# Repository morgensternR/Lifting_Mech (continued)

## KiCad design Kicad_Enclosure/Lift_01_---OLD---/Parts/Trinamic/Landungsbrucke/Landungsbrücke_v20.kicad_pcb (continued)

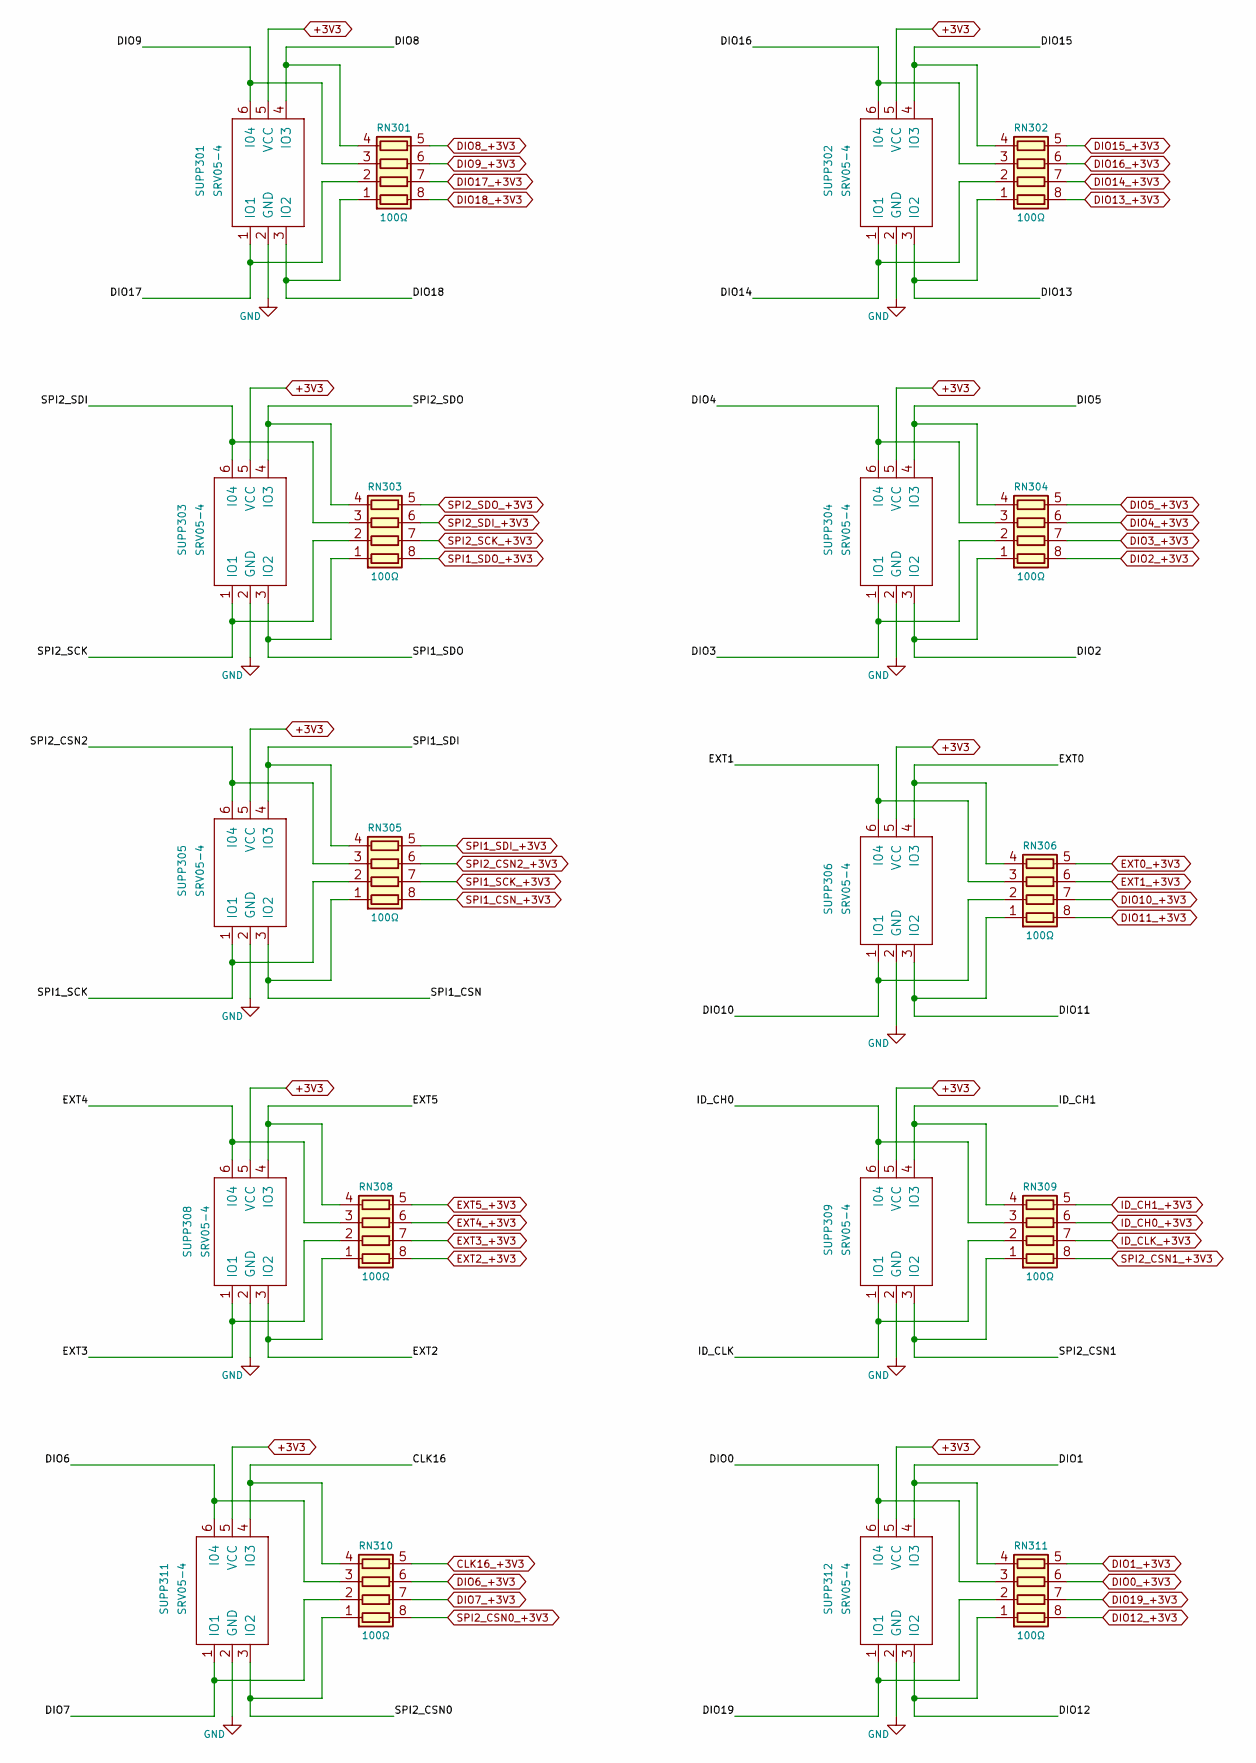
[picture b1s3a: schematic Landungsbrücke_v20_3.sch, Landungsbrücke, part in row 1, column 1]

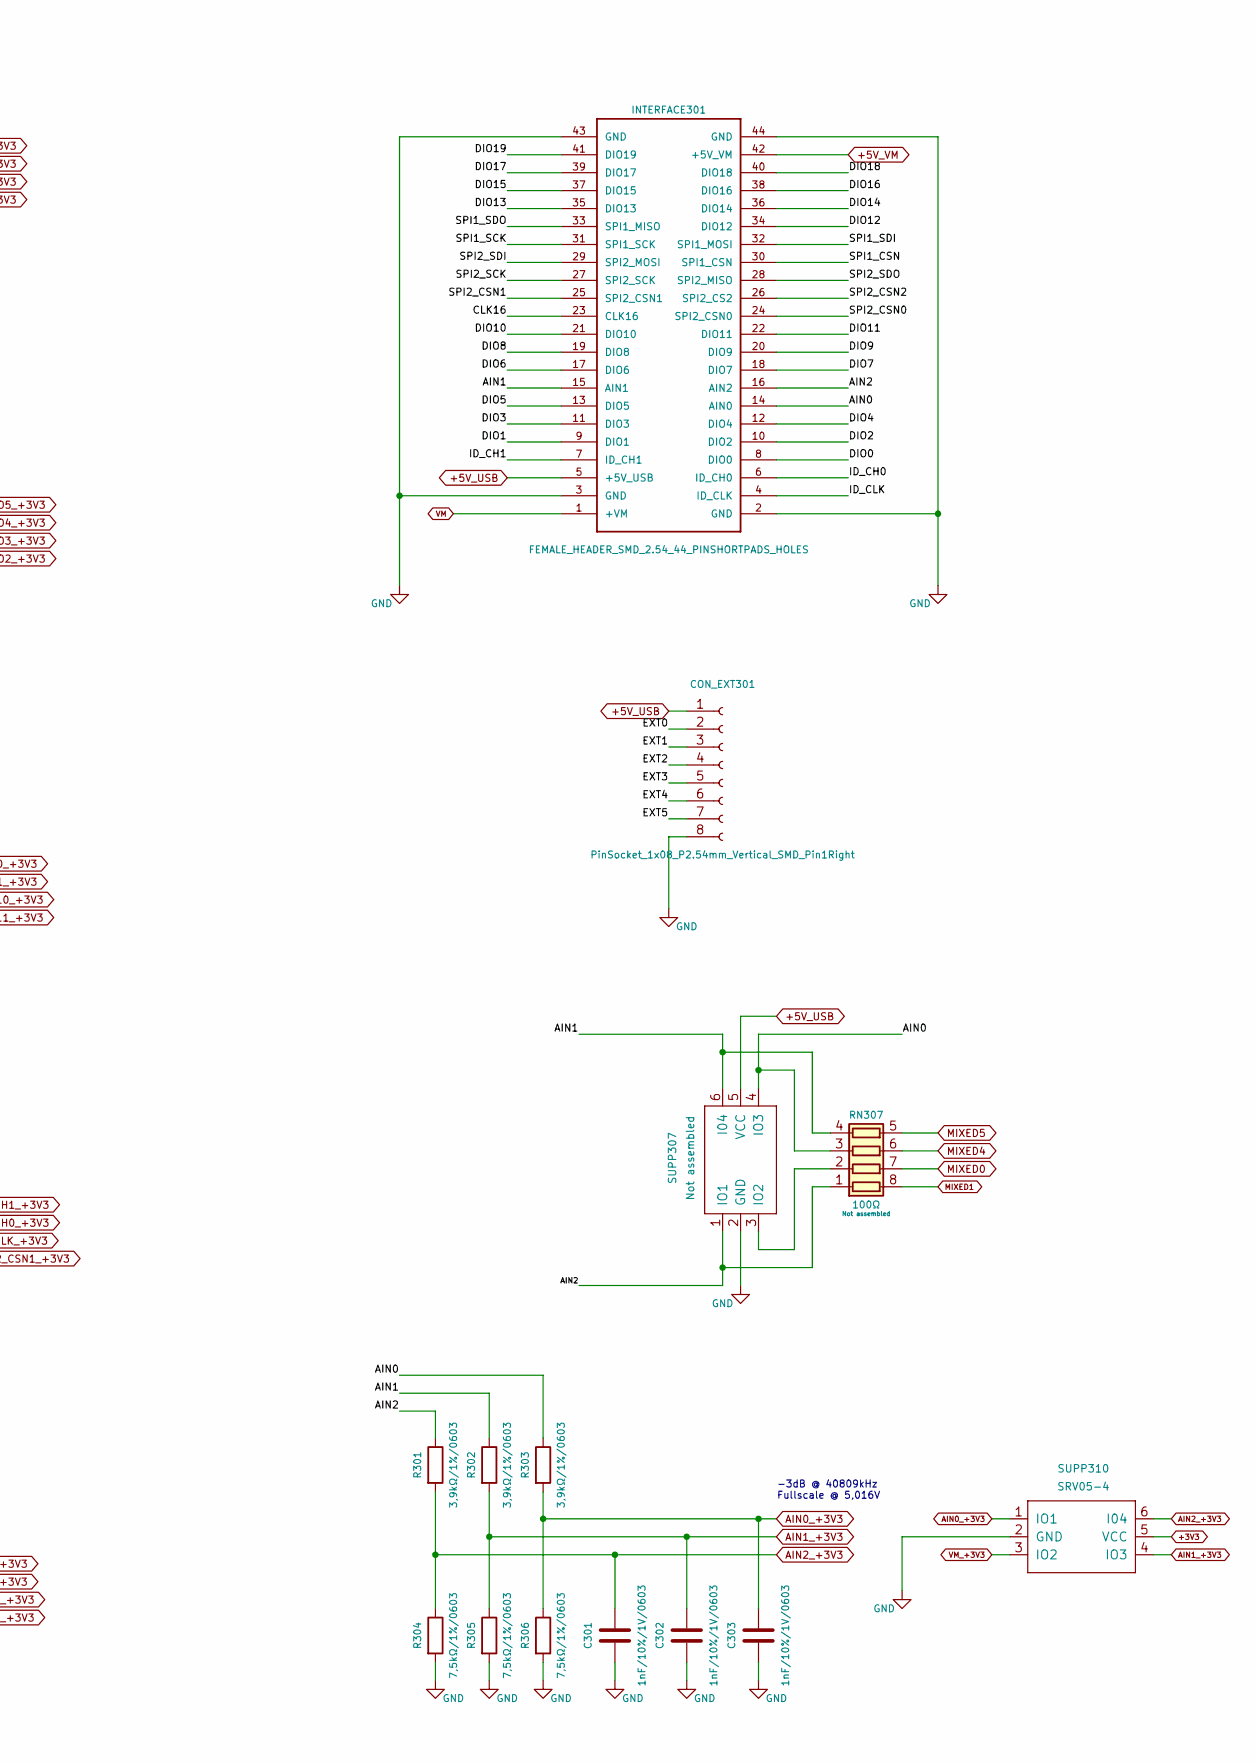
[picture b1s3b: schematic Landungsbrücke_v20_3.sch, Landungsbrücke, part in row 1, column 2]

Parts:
C301, C302, C303: 1nF/10%/1V/0603; C_0603_1608Metric
CON_EXT301: PinSocket_1x08_P2.54mm_Vertical_SMD_Pin1Right
INTERFACE301: FEMALE_HEADER_SMD_2.54_44_PINSHORTPADS_HOLES; Samtec_HLE-122-02-xxx-DV-BE-A_2x22_P2.54mm_Horizontal
R301, R302, R303: 3,9kΩ/1%/0603; R_0603_1608Metric
R304, R305, R306: 7,5kΩ/1%/0603; R_0603_1608Metric
RN301, RN302, RN303, RN304, RN305, RN306, RN307, RN308, RN309, RN310, RN311: 100Ω; R_Array_Concave_4x0603
SUPP301, SUPP302, SUPP303, SUPP304, SUPP305, SUPP306, SUPP308, SUPP309, SUPP310, SUPP311, SUPP312: SRV05-4; SOT-23-6
SUPP307: Not assembled; SOT-23-6

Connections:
+3V3: SUPP301.5 (VCC), SUPP302.5 (VCC), SUPP303.5 (VCC), SUPP304.5 (VCC), SUPP305.5 (VCC), SUPP306.5 (VCC), SUPP308.5 (VCC), SUPP309.5 (VCC), SUPP310.5 (VCC), SUPP311.5 (VCC), SUPP312.5 (VCC); also elsewhere on the board
+5V_USB: CON_EXT301.1, INTERFACE301.5 (+5V_USB), SUPP307.5 (VCC); also elsewhere on the board
+5V_VM: INTERFACE301.42 (+5V_VM); also elsewhere on the board
/Landungsbrücke_v20_3/AIN0: INTERFACE301.14 (AIN0), R303.1, RN307.3 (R3.1), SUPP307.4 (IO3)
/Landungsbrücke_v20_3/AIN1: INTERFACE301.15 (AIN1), R302.1, RN307.4 (R4.1), SUPP307.6 (I04)
/Landungsbrücke_v20_3/AIN2: INTERFACE301.16 (AIN2), R301.1, RN307.1 (R1.1), SUPP307.1 (IO1)
/Landungsbrücke_v20_3/CLK16: INTERFACE301.23 (CLK16), RN310.4 (R4.1), SUPP311.4 (IO3)
/Landungsbrücke_v20_3/DIO0: INTERFACE301.8 (DIO0), RN311.3 (R3.1), SUPP312.6 (I04)
/Landungsbrücke_v20_3/DIO1: INTERFACE301.9 (DIO1), RN311.4 (R4.1), SUPP312.4 (IO3)
/Landungsbrücke_v20_3/DIO2: INTERFACE301.10 (DIO2), RN304.1 (R1.1), SUPP304.3 (IO2)
/Landungsbrücke_v20_3/DIO3: INTERFACE301.11 (DIO3), RN304.2 (R2.1), SUPP304.1 (IO1)
/Landungsbrücke_v20_3/DIO4: INTERFACE301.12 (DIO4), RN304.3 (R3.1), SUPP304.6 (I04)
/Landungsbrücke_v20_3/DIO5: INTERFACE301.13 (DIO5), RN304.4 (R4.1), SUPP304.4 (IO3)
/Landungsbrücke_v20_3/DIO6: INTERFACE301.17 (DIO6), RN310.3 (R3.1), SUPP311.6 (I04)
/Landungsbrücke_v20_3/DIO7: INTERFACE301.18 (DIO7), RN310.2 (R2.1), SUPP311.1 (IO1)
/Landungsbrücke_v20_3/DIO8: INTERFACE301.19 (DIO8), RN301.4 (R4.1), SUPP301.4 (IO3)
/Landungsbrücke_v20_3/DIO9: INTERFACE301.20 (DIO9), RN301.3 (R3.1), SUPP301.6 (I04)
/Landungsbrücke_v20_3/DIO10: INTERFACE301.21 (DIO10), RN306.2 (R2.1), SUPP306.1 (IO1)
/Landungsbrücke_v20_3/DIO11: INTERFACE301.22 (DIO11), RN306.1 (R1.1), SUPP306.3 (IO2)
/Landungsbrücke_v20_3/DIO12: INTERFACE301.34 (DIO12), RN311.1 (R1.1), SUPP312.3 (IO2)
/Landungsbrücke_v20_3/DIO13: INTERFACE301.35 (DIO13), RN302.1 (R1.1), SUPP302.3 (IO2)
/Landungsbrücke_v20_3/DIO14: INTERFACE301.36 (DIO14), RN302.2 (R2.1), SUPP302.1 (IO1)
/Landungsbrücke_v20_3/DIO15: INTERFACE301.37 (DIO15), RN302.4 (R4.1), SUPP302.4 (IO3)
/Landungsbrücke_v20_3/DIO16: INTERFACE301.38 (DIO16), RN302.3 (R3.1), SUPP302.6 (I04)
/Landungsbrücke_v20_3/DIO17: INTERFACE301.39 (DIO17), RN301.2 (R2.1), SUPP301.1 (IO1)
/Landungsbrücke_v20_3/DIO18: INTERFACE301.40 (DIO18), RN301.1 (R1.1), SUPP301.3 (IO2)
/Landungsbrücke_v20_3/DIO19: INTERFACE301.41 (DIO19), RN311.2 (R2.1), SUPP312.1 (IO1)
/Landungsbrücke_v20_3/EXT0: CON_EXT301.2, RN306.4 (R4.1), SUPP306.4 (IO3)
/Landungsbrücke_v20_3/EXT1: CON_EXT301.3, RN306.3 (R3.1), SUPP306.6 (I04)
/Landungsbrücke_v20_3/EXT2: CON_EXT301.4, RN308.1 (R1.1), SUPP308.3 (IO2)
/Landungsbrücke_v20_3/EXT3: CON_EXT301.5, RN308.2 (R2.1), SUPP308.1 (IO1)
/Landungsbrücke_v20_3/EXT4: CON_EXT301.6, RN308.3 (R3.1), SUPP308.6 (I04)
/Landungsbrücke_v20_3/EXT5: CON_EXT301.7, RN308.4 (R4.1), SUPP308.4 (IO3)
/Landungsbrücke_v20_3/ID_CH0: INTERFACE301.6 (ID_CH0), RN309.3 (R3.1), SUPP309.6 (I04)
/Landungsbrücke_v20_3/ID_CH1: INTERFACE301.7 (ID_CH1), RN309.4 (R4.1), SUPP309.4 (IO3)
/Landungsbrücke_v20_3/ID_CLK: INTERFACE301.4 (ID_CLK), RN309.2 (R2.1), SUPP309.1 (IO1)
/Landungsbrücke_v20_3/SPI1_CSN: INTERFACE301.30 (SPI1_CSN), RN305.1 (R1.1), SUPP305.3 (IO2)
/Landungsbrücke_v20_3/SPI1_SCK: INTERFACE301.31 (SPI1_SCK), RN305.2 (R2.1), SUPP305.1 (IO1)
/Landungsbrücke_v20_3/SPI1_SDI: INTERFACE301.32 (SPI1_MOSI), RN305.4 (R4.1), SUPP305.4 (IO3)
/Landungsbrücke_v20_3/SPI1_SDO: INTERFACE301.33 (SPI1_MISO), RN303.1 (R1.1), SUPP303.3 (IO2)
/Landungsbrücke_v20_3/SPI2_CSN0: INTERFACE301.24 (SPI2_CSN0), RN310.1 (R1.1), SUPP311.3 (IO2)
/Landungsbrücke_v20_3/SPI2_CSN1: INTERFACE301.25 (SPI2_CSN1), RN309.1 (R1.1), SUPP309.3 (IO2)
/Landungsbrücke_v20_3/SPI2_CSN2: INTERFACE301.26 (SPI2_CS2), RN305.3 (R3.1), SUPP305.6 (I04)
/Landungsbrücke_v20_3/SPI2_SCK: INTERFACE301.27 (SPI2_SCK), RN303.2 (R2.1), SUPP303.1 (IO1)
/Landungsbrücke_v20_3/SPI2_SDI: INTERFACE301.29 (SPI2_MOSI), RN303.3 (R3.1), SUPP303.6 (I04)
/Landungsbrücke_v20_3/SPI2_SDO: INTERFACE301.28 (SPI2_MISO), RN303.4 (R4.1), SUPP303.4 (IO3)
AIN0_+3V3: C303.1, R303.2, R306.1, SUPP310.1 (IO1); also elsewhere on the board
AIN1_+3V3: C302.1, R302.2, R305.1, SUPP310.4 (IO3); also elsewhere on the board
AIN2_+3V3: C301.1, R301.2, R304.1, SUPP310.6 (I04); also elsewhere on the board
CLK16_+3V3: RN310.5 (R4.2); also elsewhere on the board
DIO0_+3V3: RN311.6 (R3.2); also elsewhere on the board
DIO1_+3V3: RN311.5 (R4.2); also elsewhere on the board
DIO2_+3V3: RN304.8 (R1.2); also elsewhere on the board
DIO3_+3V3: RN304.7 (R2.2); also elsewhere on the board
DIO4_+3V3: RN304.6 (R3.2); also elsewhere on the board
DIO5_+3V3: RN304.5 (R4.2); also elsewhere on the board
DIO6_+3V3: RN310.6 (R3.2); also elsewhere on the board
DIO7_+3V3: RN310.7 (R2.2); also elsewhere on the board
DIO8_+3V3: RN301.5 (R4.2); also elsewhere on the board
DIO9_+3V3: RN301.6 (R3.2); also elsewhere on the board
DIO10_+3V3: RN306.7 (R2.2); also elsewhere on the board
DIO11_+3V3: RN306.8 (R1.2); also elsewhere on the board
DIO12_+3V3: RN311.8 (R1.2); also elsewhere on the board
DIO13_+3V3: RN302.8 (R1.2); also elsewhere on the board
DIO14_+3V3: RN302.7 (R2.2); also elsewhere on the board
DIO15_+3V3: RN302.5 (R4.2); also elsewhere on the board
DIO16_+3V3: RN302.6 (R3.2); also elsewhere on the board
DIO17_+3V3: RN301.7 (R2.2); also elsewhere on the board
DIO18_+3V3: RN301.8 (R1.2); also elsewhere on the board
DIO19_+3V3: RN311.7 (R2.2); also elsewhere on the board
EXT0_+3V3: RN306.5 (R4.2); also elsewhere on the board
EXT1_+3V3: RN306.6 (R3.2); also elsewhere on the board
EXT2_+3V3: RN308.8 (R1.2); also elsewhere on the board
EXT3_+3V3: RN308.7 (R2.2); also elsewhere on the board
EXT4_+3V3: RN308.6 (R3.2); also elsewhere on the board
EXT5_+3V3: RN308.5 (R4.2); also elsewhere on the board
GND: C301.2, C302.2, C303.2, CON_EXT301.8, INTERFACE301.2 (GND), INTERFACE301.3 (GND), INTERFACE301.43 (GND), INTERFACE301.44 (GND), R304.2, R305.2, R306.2, SUPP301.2 (GND), SUPP302.2 (GND), SUPP303.2 (GND), SUPP304.2 (GND), SUPP305.2 (GND), SUPP306.2 (GND), SUPP307.2 (GND), SUPP308.2 (GND), SUPP309.2 (GND), SUPP310.2 (GND), SUPP311.2 (GND), SUPP312.2 (GND); also elsewhere on the board
ID_CH0_+3V3: RN309.6 (R3.2); also elsewhere on the board
ID_CH1_+3V3: RN309.5 (R4.2); also elsewhere on the board
ID_CLK_+3V3: RN309.7 (R2.2); also elsewhere on the board
MIXED0: RN307.7 (R2.2); also elsewhere on the board
MIXED1: RN307.8 (R1.2); also elsewhere on the board
MIXED4: RN307.6 (R3.2); also elsewhere on the board
MIXED5: RN307.5 (R4.2); also elsewhere on the board
unnamed: RN307.2 (R2.1), SUPP307.3 (IO2)
SPI1_CSN_+3V3: RN305.8 (R1.2); also elsewhere on the board
SPI1_SCK_+3V3: RN305.7 (R2.2); also elsewhere on the board
SPI1_SDI_+3V3: RN305.5 (R4.2); also elsewhere on the board
SPI1_SDO_+3V3: RN303.8 (R1.2); also elsewhere on the board
SPI2_CSN0_+3V3: RN310.8 (R1.2); also elsewhere on the board
SPI2_CSN1_+3V3: RN309.8 (R1.2); also elsewhere on the board
SPI2_CSN2_+3V3: RN305.6 (R3.2); also elsewhere on the board
SPI2_SCK_+3V3: RN303.7 (R2.2); also elsewhere on the board
SPI2_SDI_+3V3: RN303.6 (R3.2); also elsewhere on the board
SPI2_SDO_+3V3: RN303.5 (R4.2); also elsewhere on the board
VM: INTERFACE301.1 (+VM); also elsewhere on the board
VM_+3V3: SUPP310.3 (IO2); also elsewhere on the board

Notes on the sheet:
-3dB @ 40809kHz Fullscale @ 5,016V

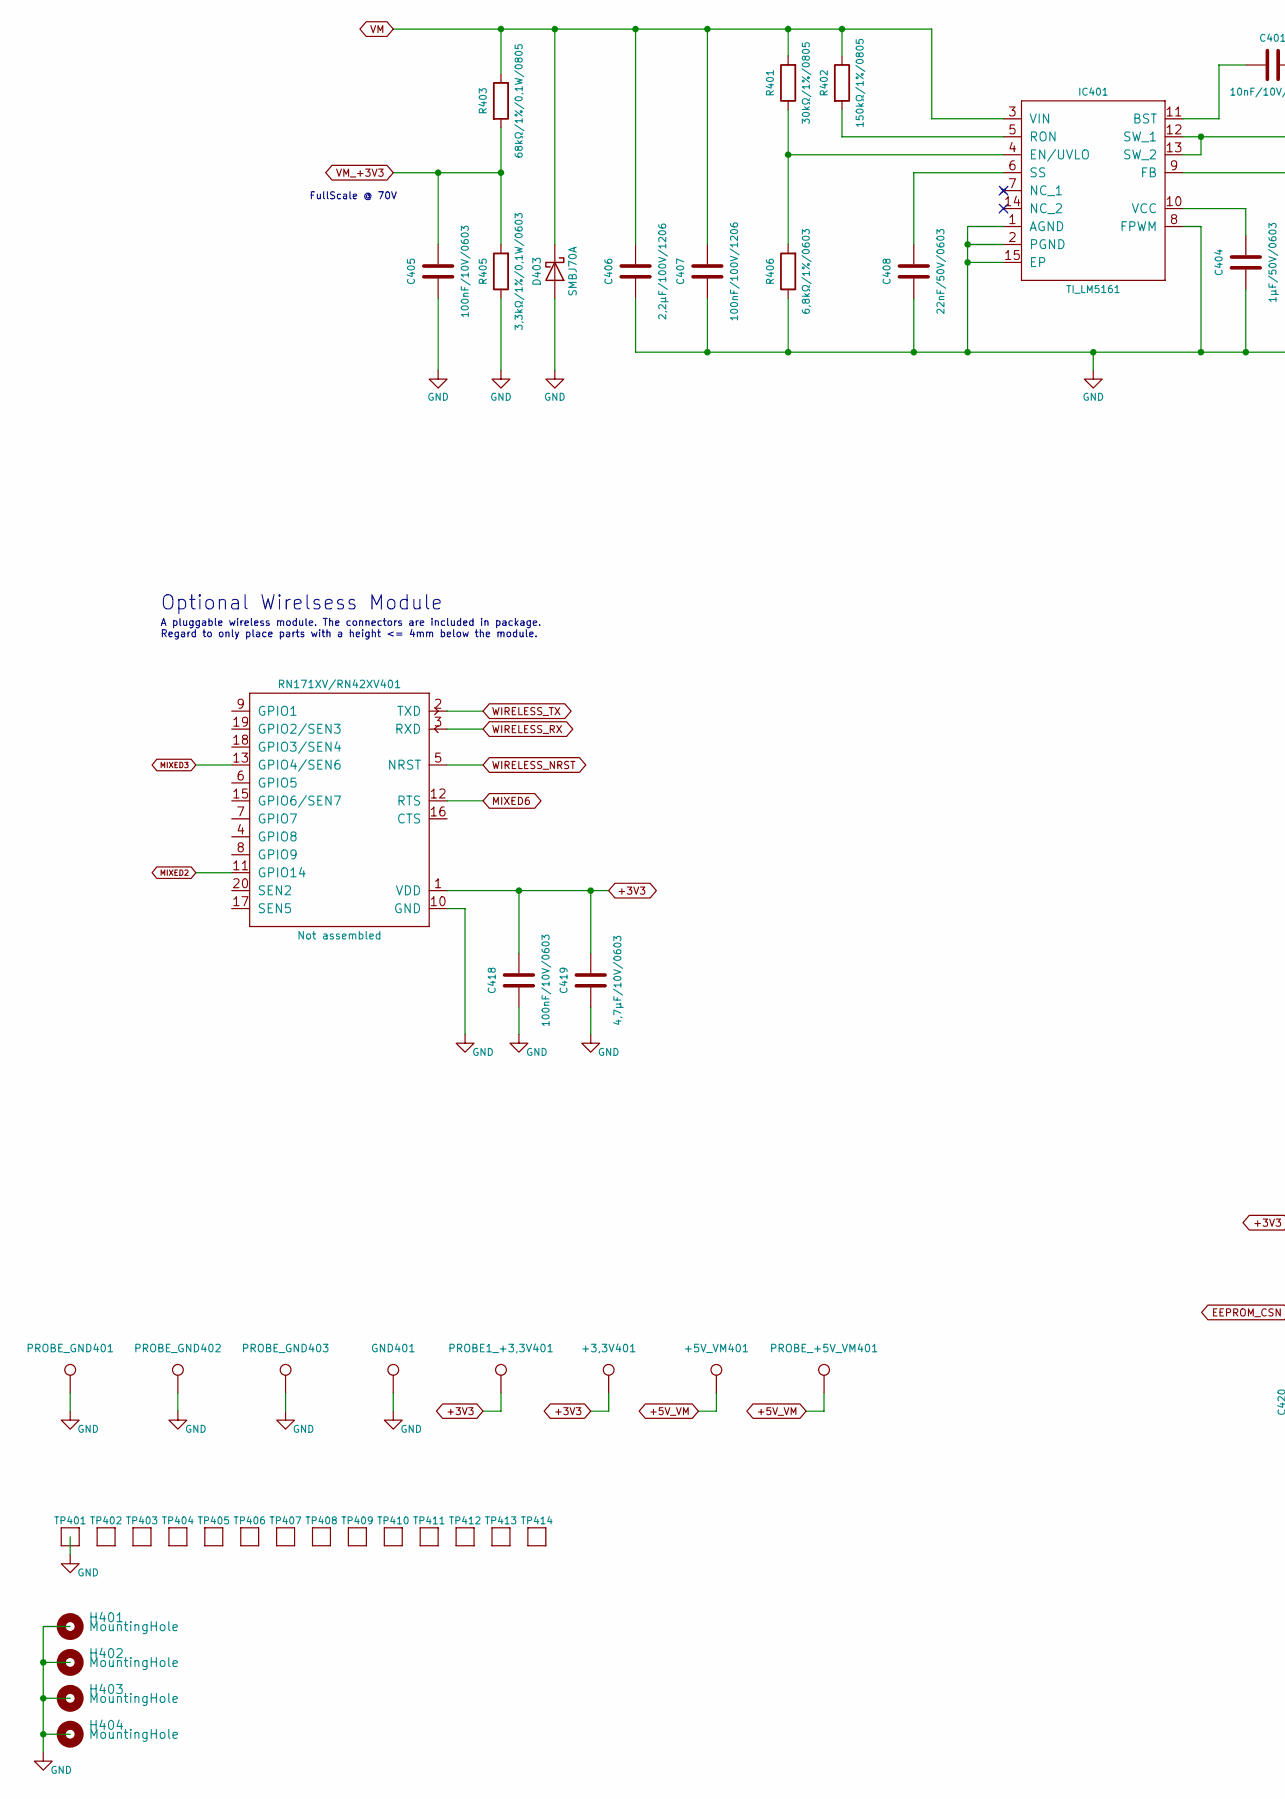
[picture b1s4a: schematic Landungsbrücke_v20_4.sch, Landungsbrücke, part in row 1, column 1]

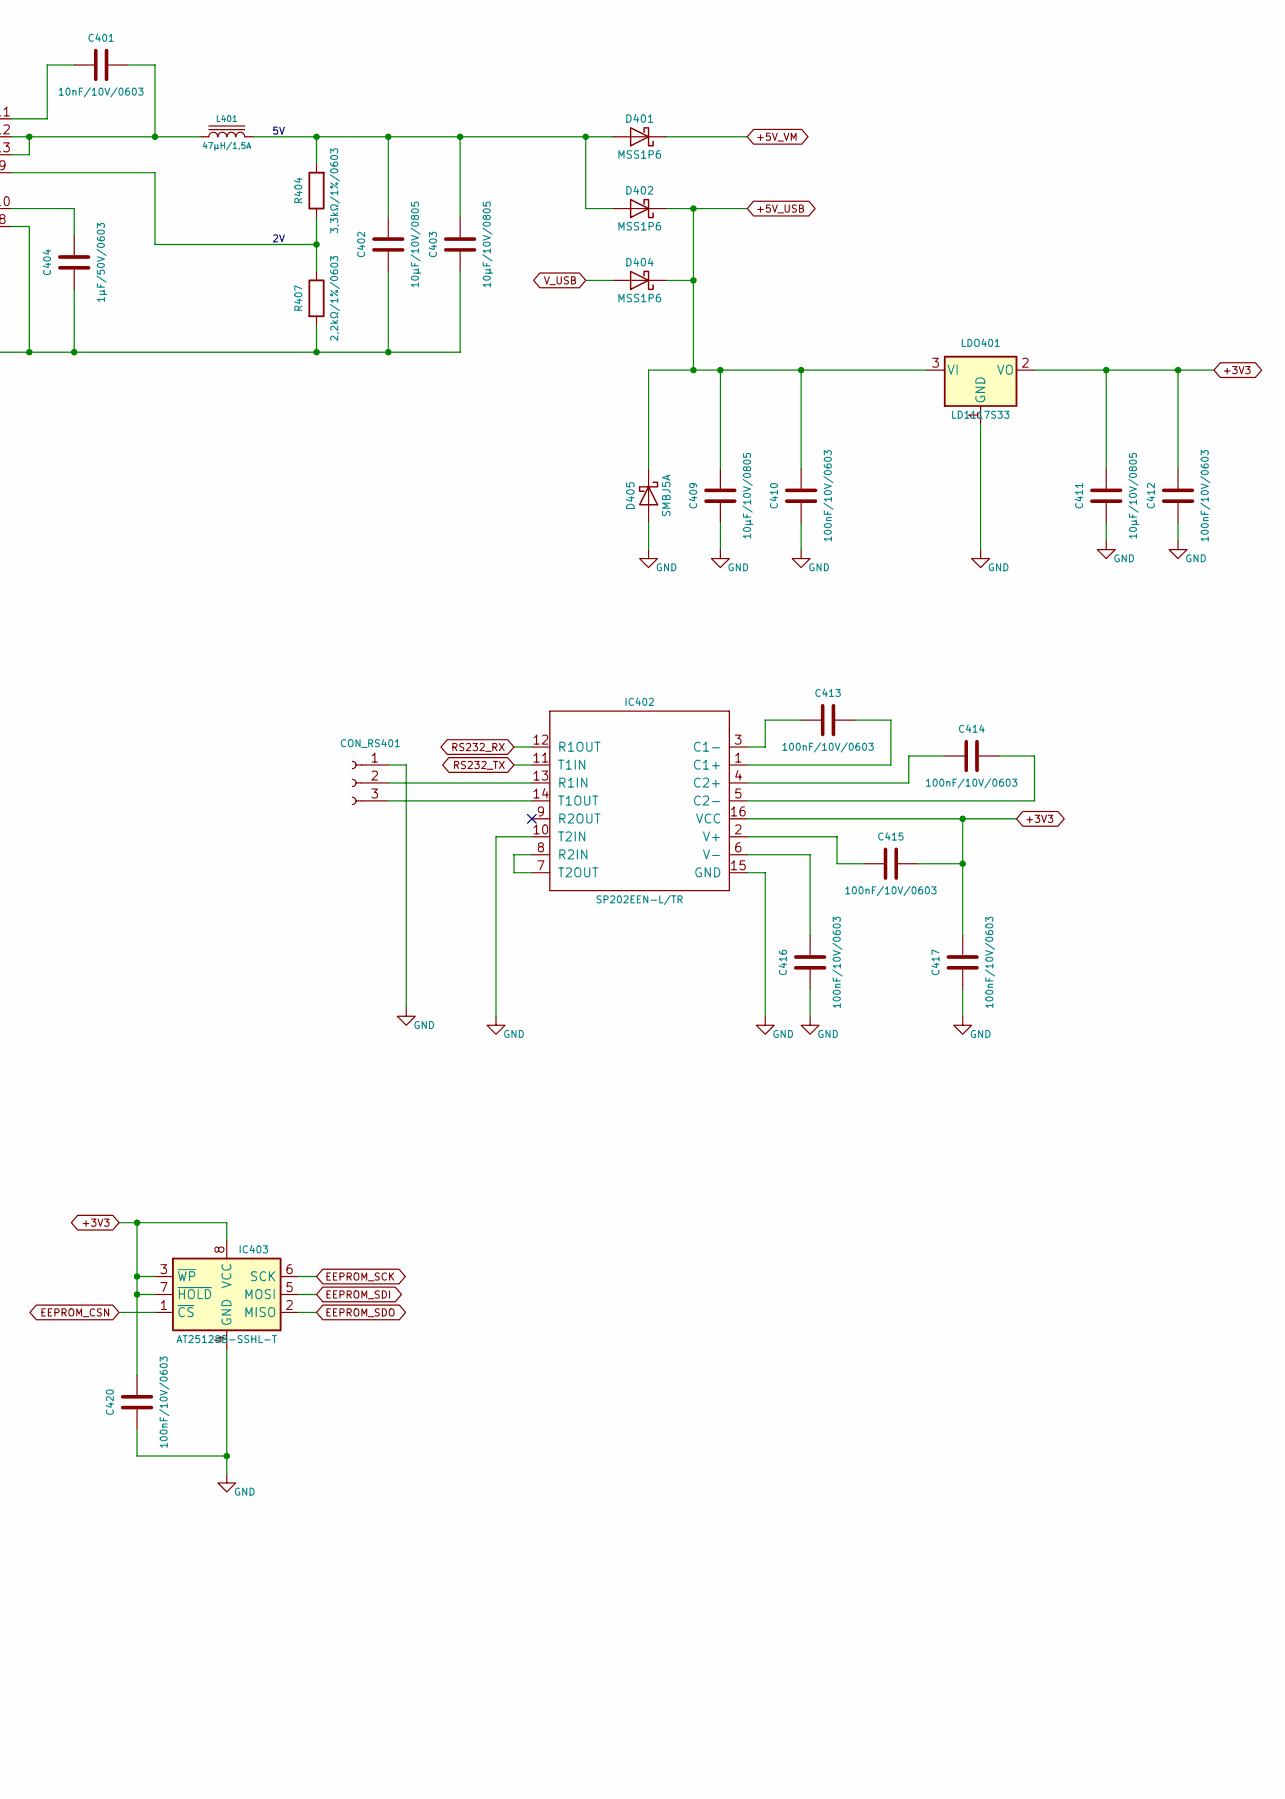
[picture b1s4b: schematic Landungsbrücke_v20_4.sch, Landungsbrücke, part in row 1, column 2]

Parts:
+3,3V401: 1PIN_1ROW; TestPoint_Loop_D1.80mm_Drill1.0mm_Beaded
+5V_VM401: Not assembled; TestPoint_Loop_D1.80mm_Drill1.0mm_Beaded
C401: 10nF/10V/0603; C_0603_1608Metric
C402, C403, C409, C411: 10μF/10V/0805; C_0805_2012Metric
C404: 1μF/50V/0603; C_0603_1608Metric
C405, C410, C412, C413, C414, C415, C416, C417, C418, C420: 100nF/10V/0603; C_0603_1608Metric
C406: 2,2μF/100V/1206; C_1206_3216Metric
C407: 100nF/100V/1206; C_1206_3216Metric
C408: 22nF/50V/0603; C_0603_1608Metric
C419: 4,7µF/10V/0603; C_0603_1608Metric
CON_RS401: PinSocket_1x03_P2.54mm_Vertical_SMD_Pin1Right
D401, D402, D404: MSS1P6; D_TUMD2
D403: SMBJ70A; D_SMB
D405: SMBJ5A; D_SMB
GND401: 1PIN_1ROW; TestPoint_Loop_D1.80mm_Drill1.0mm_Beaded
H401, H402, H403, H404: MountingHole; MountingHole_3.2mm_M3_Pad
IC401: TI_LM5161; TSSOP-14-1EP_4.4x5mm_P0.65mm
IC402: SP202EEN-L/TR; SOIC-16_3.9x9.9mm_P1.27mm
IC403: AT25128B-SSHL-T; SO-8_3.9x4.9mm_P1.27mm
L401: 47μH/1,5A; L_Bourns-SRU8043
LDO401: LD1117S33; SOT-223-3_TabPin2
PROBE1_+3,3V401: Not assembled; TestPoint_Loop_D1.80mm_Drill1.0mm_Beaded
PROBE_+5V_VM401: 1PIN_1ROW; TestPoint_Loop_D1.80mm_Drill1.0mm_Beaded
PROBE_GND401, PROBE_GND402, PROBE_GND403: Not assembled; TestPoint_Loop_D1.80mm_Drill1.0mm_Beaded
R401: 30kΩ/1%/0805; R_0805_2012Metric
R402: 150kΩ/1%/0805; R_0805_2012Metric
R403: 68kΩ/1%/0,1W/0805; R_0805_2012Metric
R404: 3,3kΩ/1%/0603; R_0603_1608Metric
R405: 3,3kΩ/1%/0,1W/0603; R_0603_1608Metric
R406: 6,8kΩ/1%/0603; R_0603_1608Metric
R407: 2,2kΩ/1%/0603; R_0603_1608Metric
RN171XV/RN42XV401: Not assembled; Radio_module
TP401, TP402, TP403, TP404, TP405, TP406, TP407, TP408, TP409, TP410, TP411, TP412, TP413, TP414: Not assembled; PAD_R1.2

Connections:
+3V3: +3,3V401.1, C411.1, C412.1, C415.1, C417.1, C418.1, C419.1, C420.2, IC402.16 (VCC), IC403.3 (~WP), IC403.7 (~HOLD), IC403.8 (VCC), LDO401.2 (VO), PROBE1_+3,3V401.1, RN171XV/RN42XV401.1 (VDD); also elsewhere on the board
+5V_USB: C409.1, C410.1, D402.1 (K), D404.1 (K), D405.1 (K), LDO401.3 (VI); also elsewhere on the board
+5V_VM: +5V_VM401.1, D401.1 (K), PROBE_+5V_VM401.1; also elsewhere on the board
EEPROM_CSN: IC403.1 (~CS); also elsewhere on the board
EEPROM_SCK: IC403.6 (SCK); also elsewhere on the board
EEPROM_SDI: IC403.5 (MOSI); also elsewhere on the board
EEPROM_SDO: IC403.2 (MISO); also elsewhere on the board
GND: C402.2, C403.2, C404.2, C405.2, C406.2, C407.2, C408.2, C409.2, C410.2, C411.2, C412.2, C416.2, C417.2, C418.2, C419.2, C420.1, CON_RS401.1, D403.2 (A), D405.2 (A), GND401.1, H401.~, H402.~, H403.~, H404.~, IC401.1 (AGND), IC401.2 (PGND), IC401.8 (FPWM), IC401.15 (EP), IC402.10 (T2IN), IC402.15 (GND), IC403.4 (GND), LDO401.1 (GND), PROBE_GND401.1, PROBE_GND402.1, PROBE_GND403.1, R405.1, R406.1, R407.2, RN171XV/RN42XV401.10 (GND), TP401.P$1; also elsewhere on the board
MIXED2: RN171XV/RN42XV401.11 (GPIO14); also elsewhere on the board
MIXED3: RN171XV/RN42XV401.13 (GPIO4/SEN6); also elsewhere on the board
MIXED6: RN171XV/RN42XV401.12 (RTS); also elsewhere on the board
unnamed: C401.1, IC401.12 (SW_1), IC401.13 (SW_2), L401.1
unnamed: C401.2, IC401.11 (BST)
unnamed: C402.1, C403.1, D401.2 (A), D402.2 (A), L401.2, R404.2
unnamed: C404.1, IC401.10 (VCC)
unnamed: C408.1, IC401.6 (SS)
unnamed: C413.1, IC402.1 (C1+)
unnamed: C413.2, IC402.3 (C1-)
unnamed: C414.1, IC402.5 (C2-)
unnamed: C414.2, IC402.4 (C2+)
unnamed: C415.2, IC402.2 (V+)
unnamed: C416.1, IC402.6 (V-)
unnamed: CON_RS401.2, IC402.13 (R1IN)
unnamed: CON_RS401.3, IC402.14 (T1OUT)
unnamed: IC401.4 (EN/UVLO), R401.1, R406.2
unnamed: IC401.5 (RON), R402.2
unnamed: IC401.9 (FB), R404.1, R407.1
unnamed: IC402.7 (T2OUT), IC402.8 (R2IN)
RS232_RX: IC402.12 (R1OUT); also elsewhere on the board
RS232_TX: IC402.11 (T1IN); also elsewhere on the board
VM: C406.1, C407.1, D403.1 (K), IC401.3 (VIN), R401.2, R402.1, R403.1; also elsewhere on the board
VM_+3V3: C405.1, R403.2, R405.2; also elsewhere on the board
V_USB: D404.2 (A); also elsewhere on the board
WIRELESS_NRST: RN171XV/RN42XV401.5 (NRST); also elsewhere on the board
WIRELESS_RX: RN171XV/RN42XV401.3 (RXD); also elsewhere on the board
WIRELESS_TX: RN171XV/RN42XV401.2 (TXD); also elsewhere on the board

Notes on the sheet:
FullScale @ 70V
Optional Wirelsess Module
A pluggable wireless module. The connectors are included in package. Regard to only place parts with a height <= 4mm below the module.

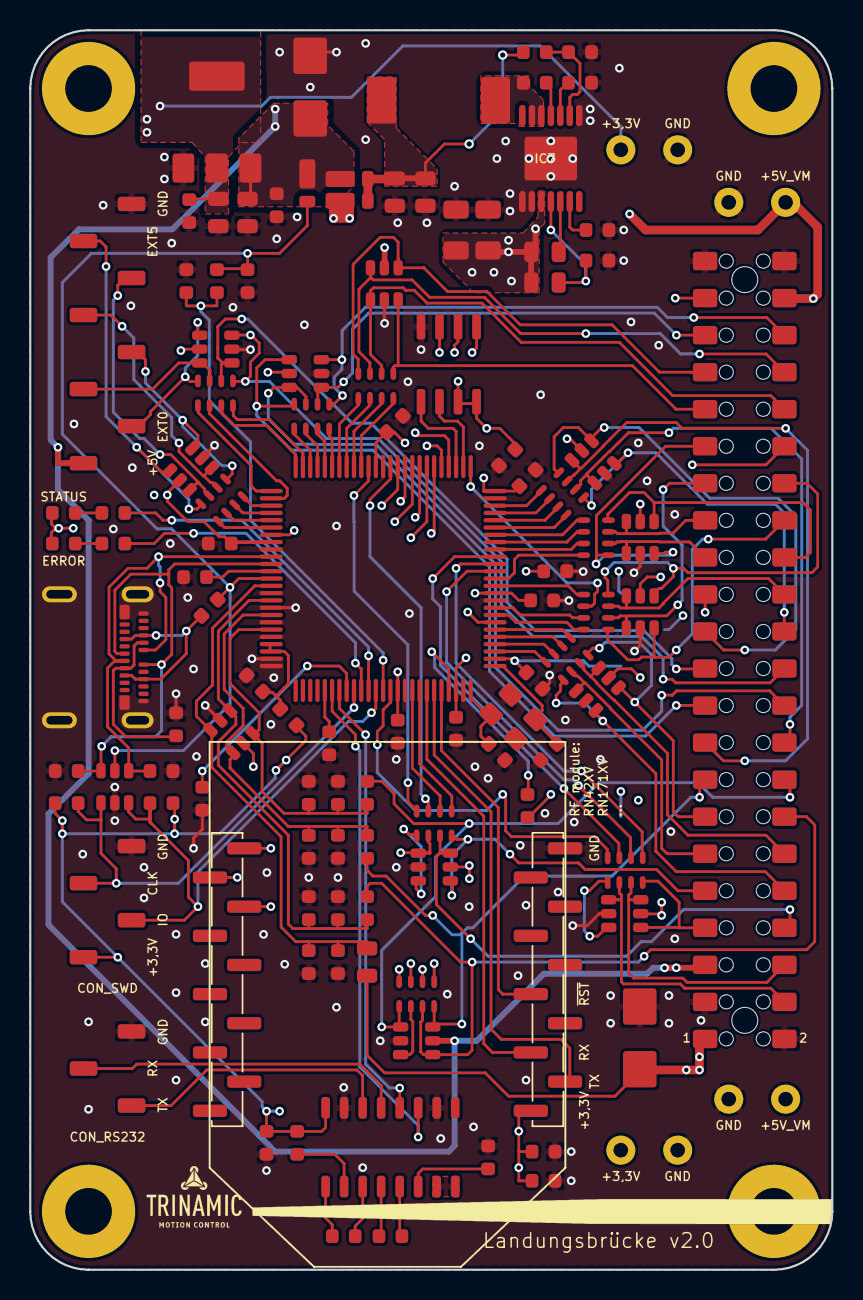
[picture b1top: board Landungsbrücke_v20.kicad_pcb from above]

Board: 4 copper layers, 55.0 x 85.0 mm, 138 parts (0 on the bottom side), 147 nets.

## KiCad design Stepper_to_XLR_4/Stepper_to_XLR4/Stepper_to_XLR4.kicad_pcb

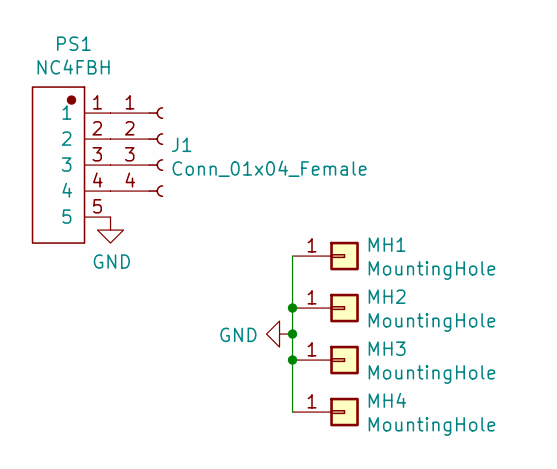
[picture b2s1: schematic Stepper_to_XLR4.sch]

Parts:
J1: Conn_01x04_Female; 1x4 Hole Header_4mm
MH1, MH2, MH3, MH4: MountingHole; MountingHole_3.2mm_M3
PS1: NC4FBH; CONN-TH_NC4FBH_XLR4_Female_RA_Panel; LCSC C368478

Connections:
GND: MH1.1, MH2.1, MH3.1, MH4.1, PS1.5
unnamed: J1.1, PS1.1
unnamed: J1.2, PS1.2
unnamed: J1.3, PS1.3
unnamed: J1.4, PS1.4

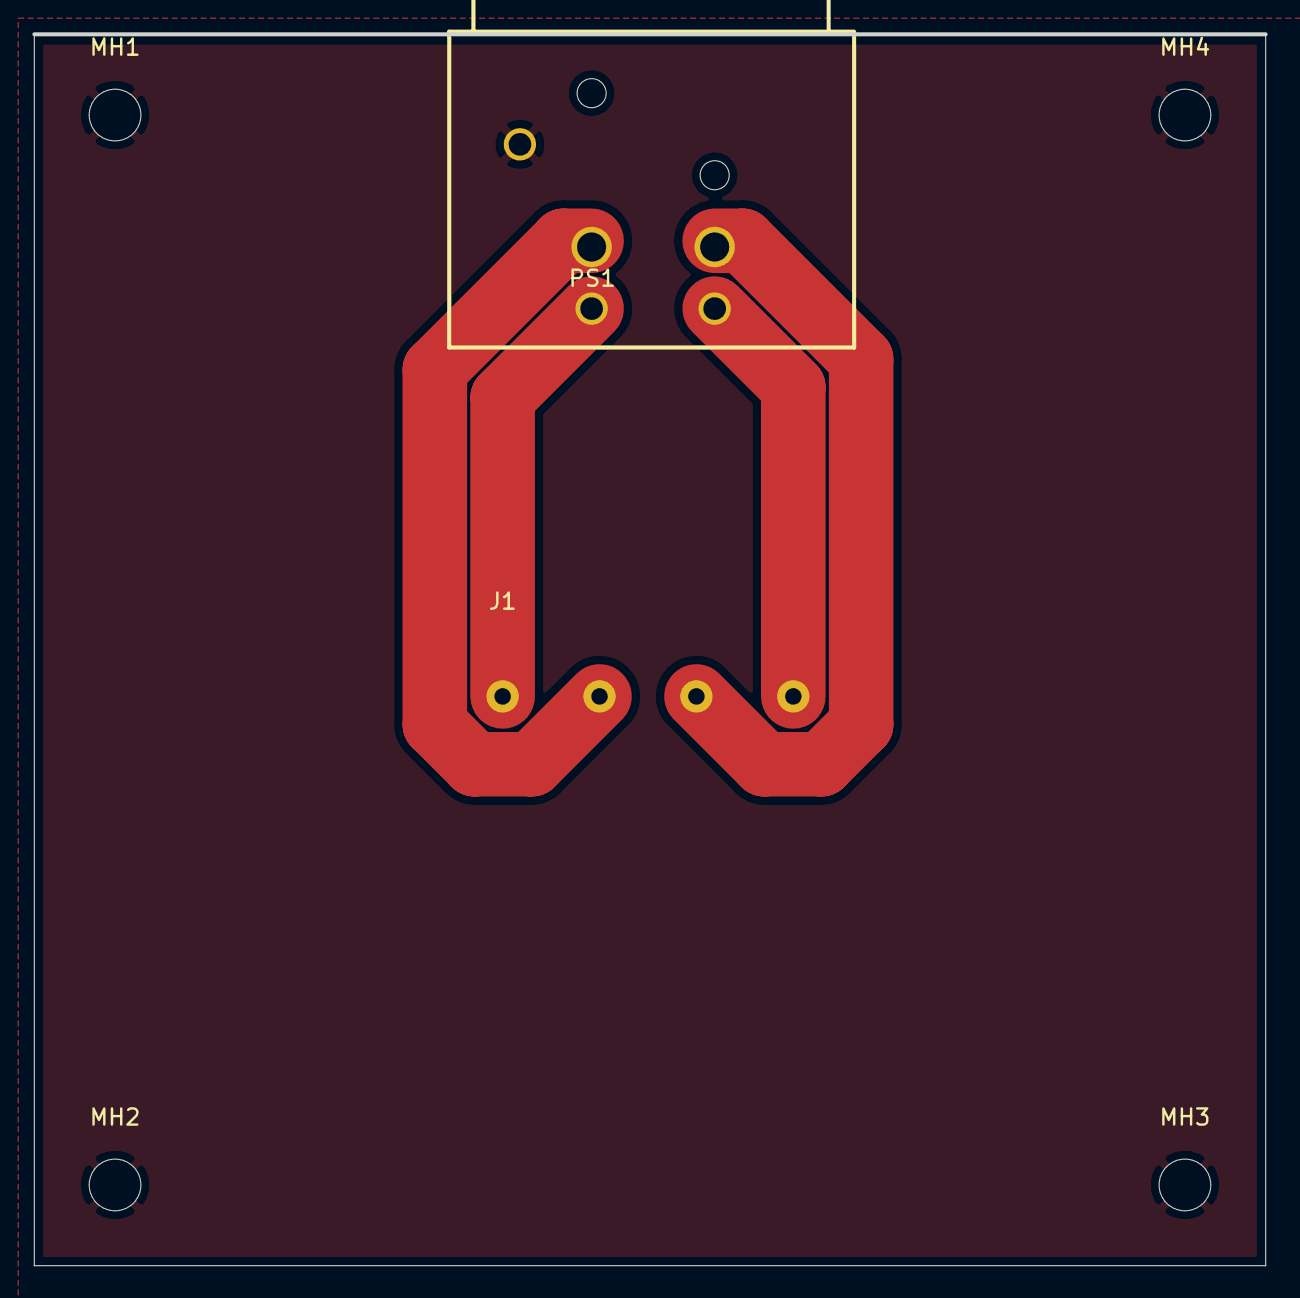
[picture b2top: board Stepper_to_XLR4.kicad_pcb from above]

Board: 2 copper layers, 76.2 x 76.2 mm, 6 parts (0 on the bottom side), 5 nets.

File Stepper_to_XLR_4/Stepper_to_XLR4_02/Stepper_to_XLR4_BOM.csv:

Comment,Designator,Footprint,LCSC
"Conn_01x04_Female","J1","Connector:1x4 Hole Header_4mm",""
"MountingHole","MH1,MH2,MH3,MH4","MountingHole:MountingHole_3.2mm_M3",""
"NC4FBH","PS1","Connector:CONN-TH_NC4FBH_XLR4_Female_RA_Panel","C368478"
